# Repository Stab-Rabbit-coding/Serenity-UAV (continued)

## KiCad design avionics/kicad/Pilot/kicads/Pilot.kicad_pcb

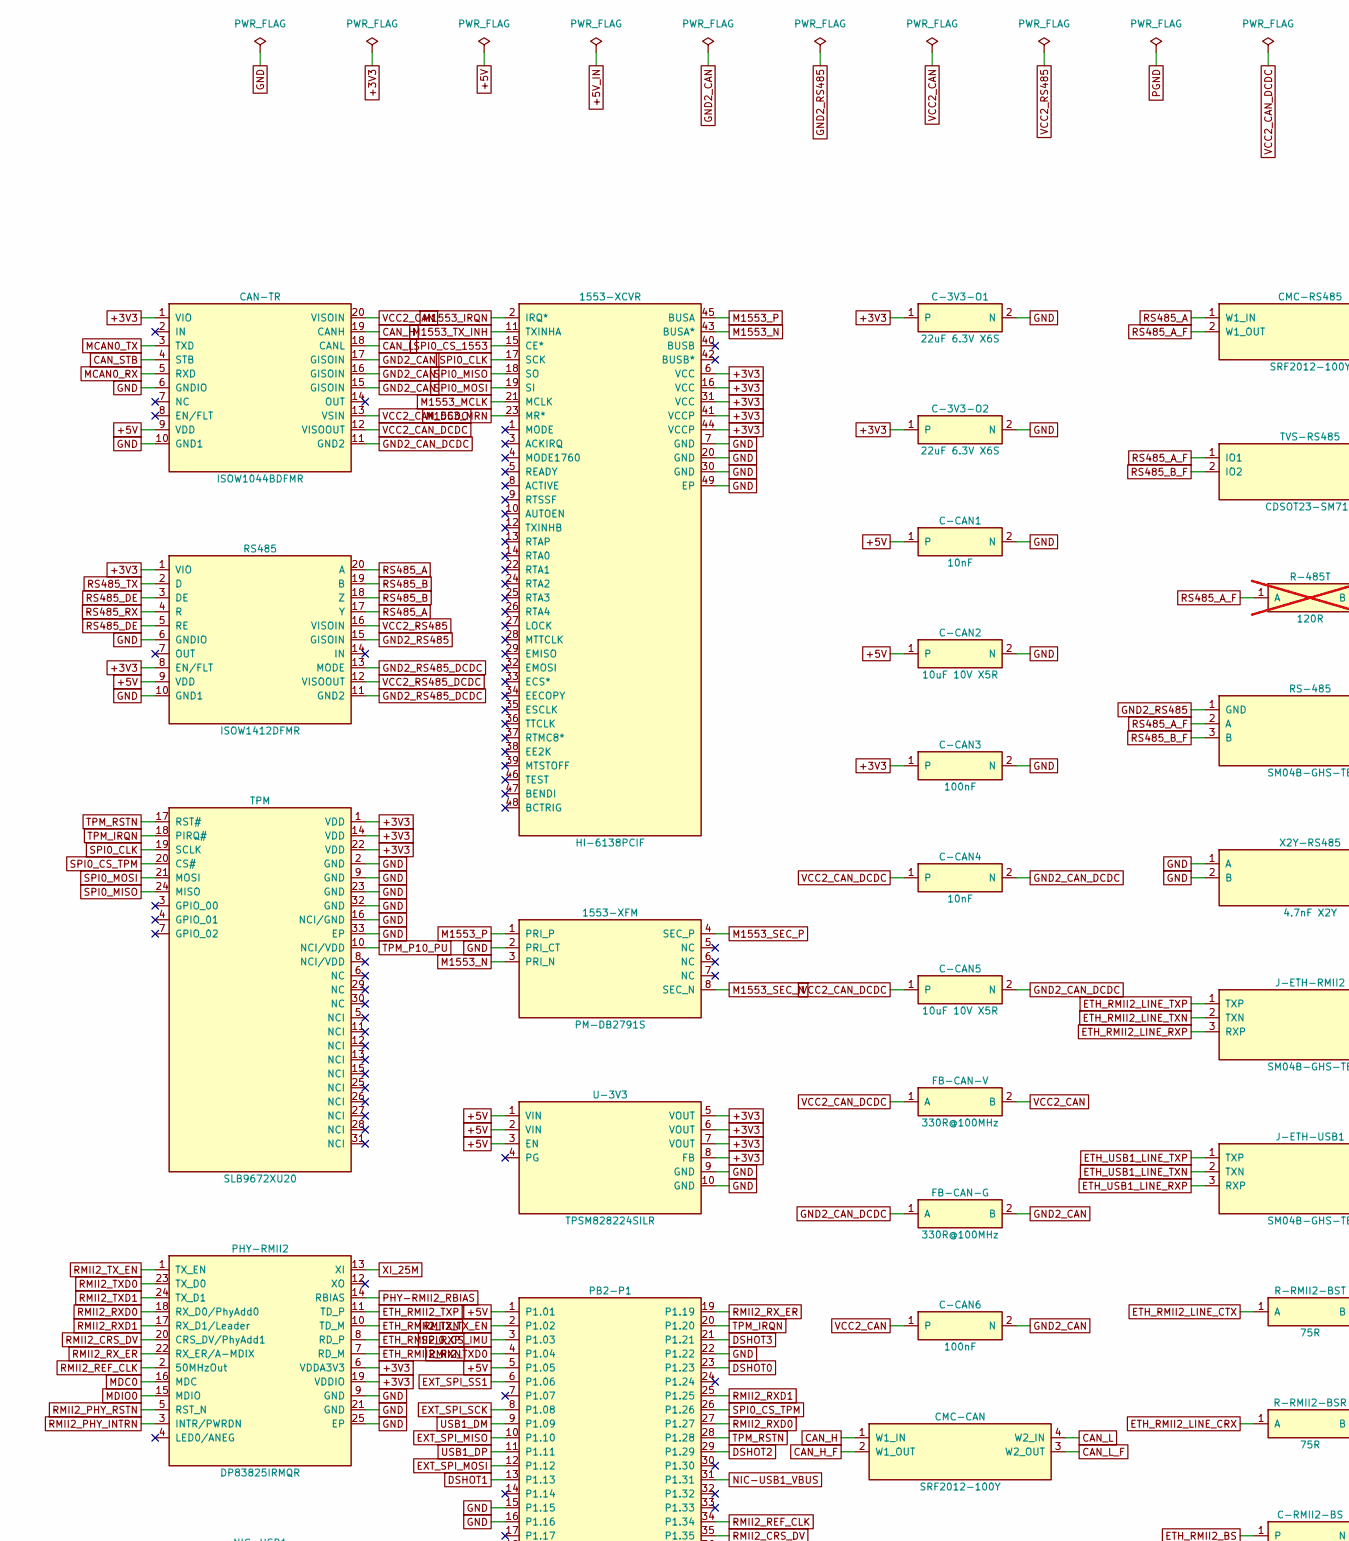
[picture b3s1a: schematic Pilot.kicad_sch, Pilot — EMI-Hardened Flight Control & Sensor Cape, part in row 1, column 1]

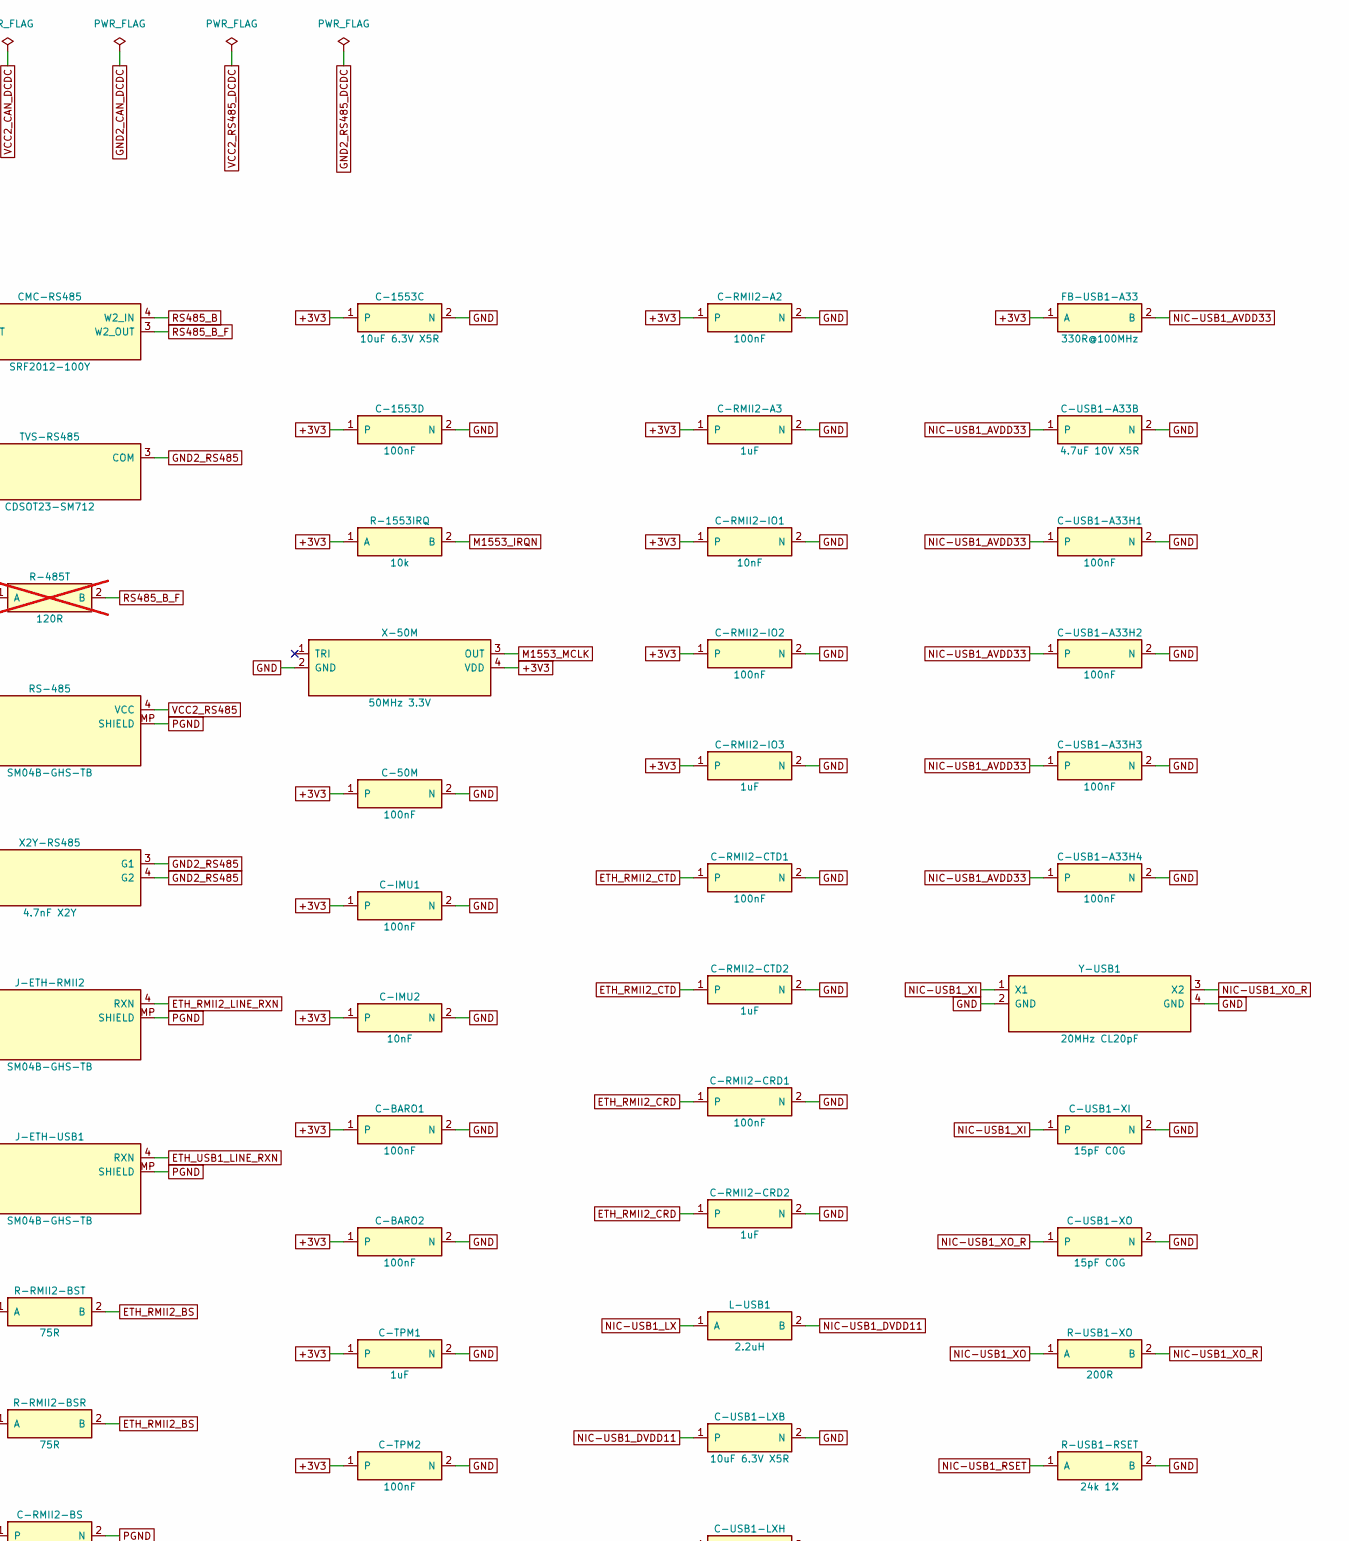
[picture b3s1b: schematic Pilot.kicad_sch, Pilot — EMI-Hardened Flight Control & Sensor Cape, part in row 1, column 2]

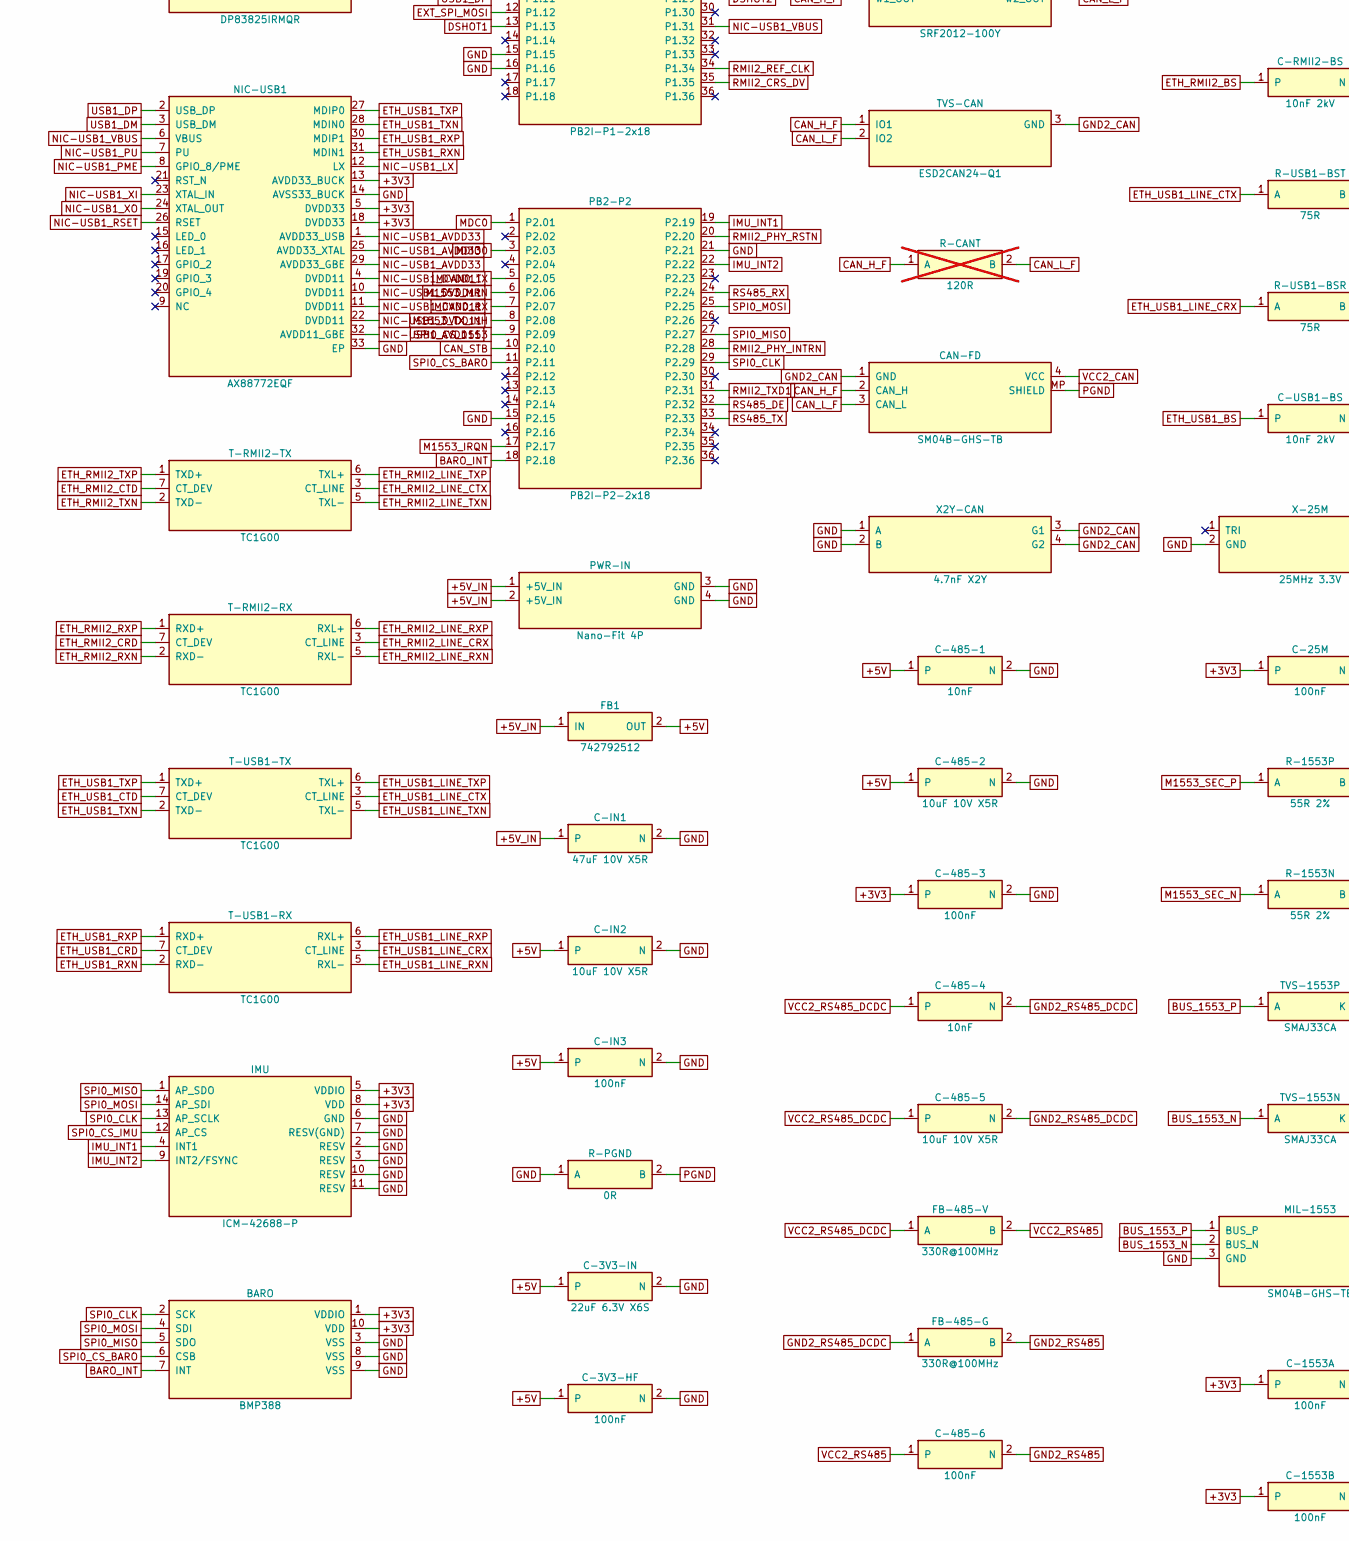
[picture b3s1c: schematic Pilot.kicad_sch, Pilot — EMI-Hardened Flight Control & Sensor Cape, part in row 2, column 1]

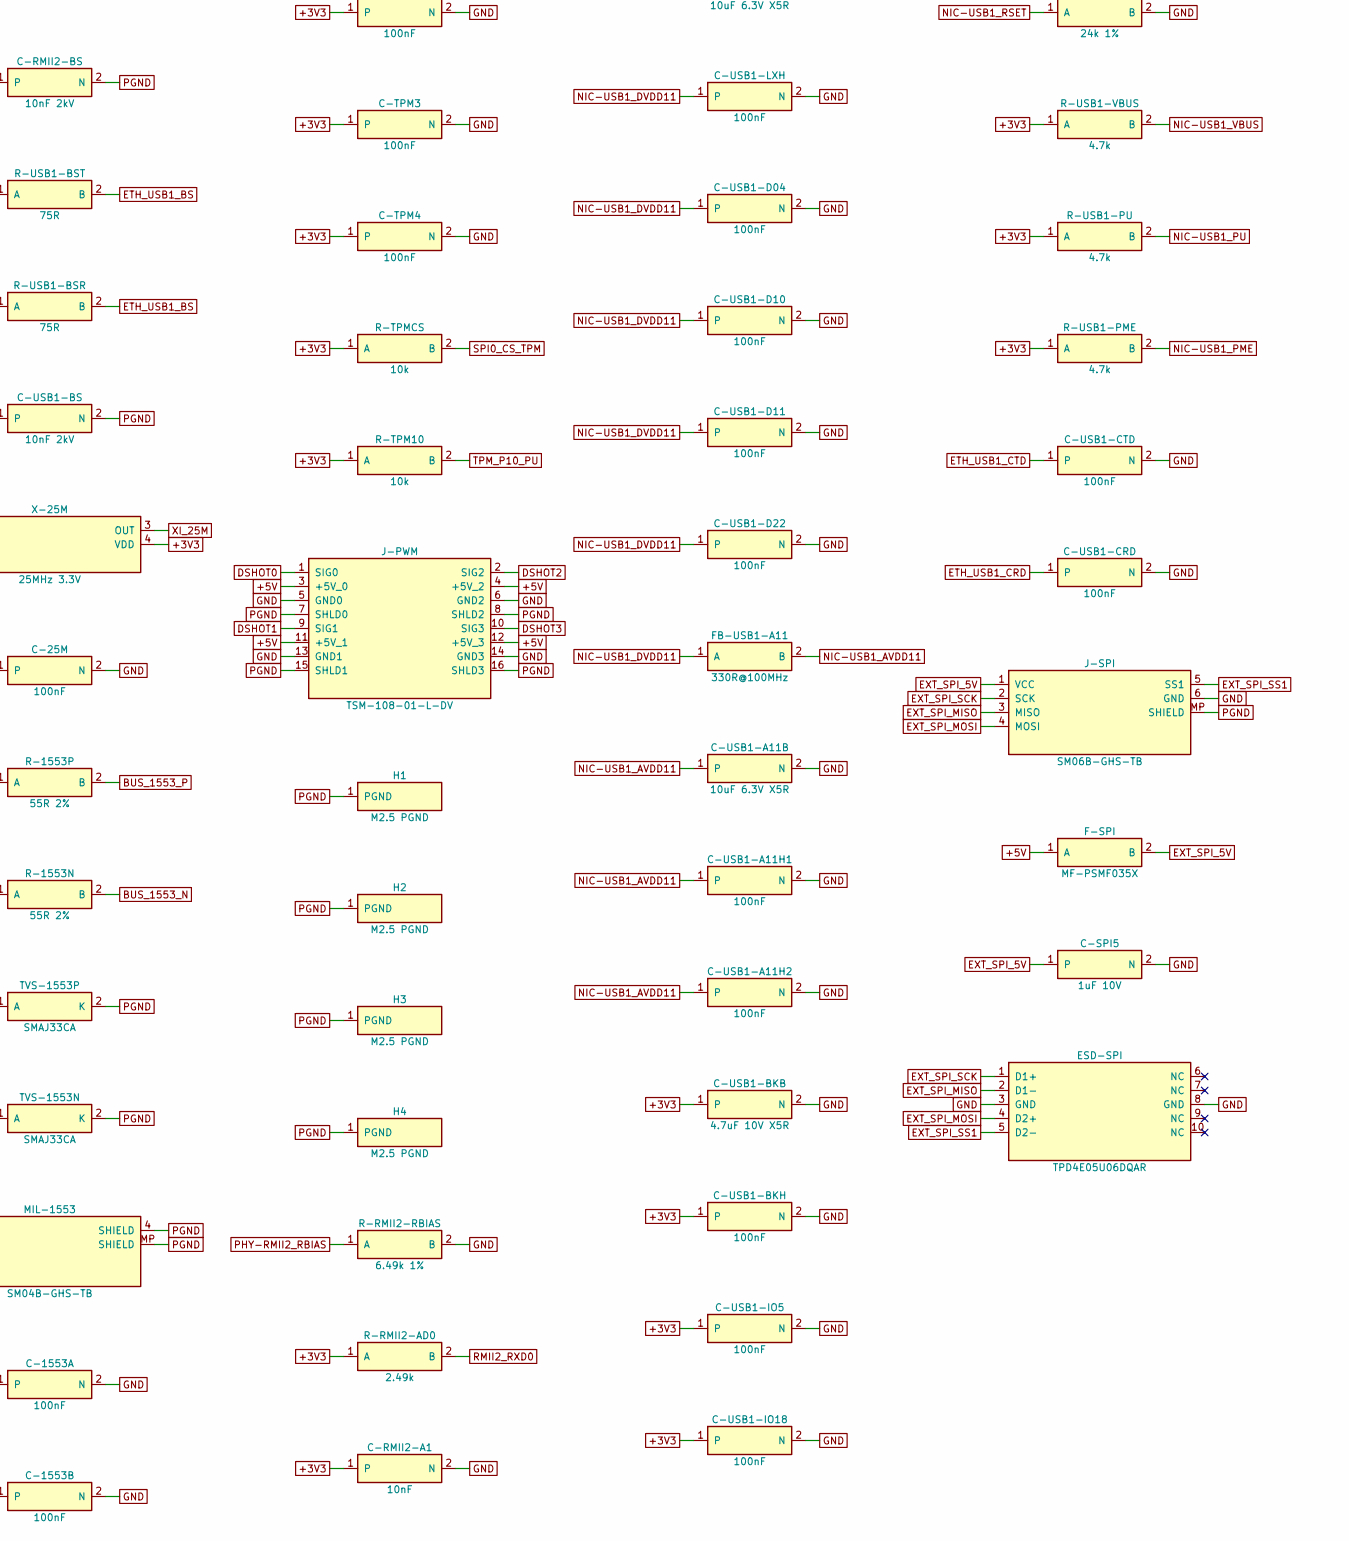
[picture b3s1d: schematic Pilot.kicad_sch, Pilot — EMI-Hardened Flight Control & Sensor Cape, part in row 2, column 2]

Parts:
1553-XCVR: HI-6138PCIF; Holt_HI-6138_QFN-48_6x6mm_P0.4mm_EP4.6mm; MPN HI-6138PCIF
1553-XFM: PM-DB2791S; Xfmr_1553_SMD_0.40in_8pin; MPN PM-DB2791S
BARO: BMP388; Bosch_BMP388_LGA-10_2x2mm; MPN BMP388
C-3V3-HF, C-25M, C-50M, C-485-3, C-485-6, C-1553A, C-1553B, C-1553D: 100nF; C_0402_1005Metric; MPN CC0402KRX7R7BB104
C-3V3-IN, C-3V3-O1, C-3V3-O2: 22uF 6.3V X6S; C_0603_1608Metric; MPN MSASJ168BC6226MTNA01
C-485-1, C-485-4: 10nF; C_0402_1005Metric; MPN CC0402KRX7R7BB103
C-485-2, C-485-5: 10uF 10V X5R; C_0805_2012Metric; MPN CC0805KKX5R6BB106
C-1553C: 10uF 6.3V X5R; C_0805_2012Metric; MPN CC0805KKX5R6BB106
C-BARO1, C-BARO2: 100nF; C_0402_1005Metric; MPN CC0402KRX7R7BB104
C-CAN1, C-CAN4: 10nF; C_0402_1005Metric; MPN CC0402KRX7R7BB103
C-CAN2, C-CAN5: 10uF 10V X5R; C_0805_2012Metric; MPN CC0805KKX5R6BB106
C-CAN3, C-CAN6: 100nF; C_0402_1005Metric; MPN CC0402KRX7R7BB104
C-IMU1: 100nF; C_0402_1005Metric; MPN CC0402KRX7R7BB104
C-IMU2: 10nF; C_0201_0603Metric; MPN CC0201KRX7R7BB103
C-IN1: 47uF 10V X5R; C_1210_3225Metric; MPN LMK325BJ476KMHP
C-IN2: 10uF 10V X5R; C_0805_2012Metric; MPN CC0805KKX5R6BB106
C-IN3: 100nF; C_0402_1005Metric; MPN CC0402KRX7R7BB104
C-RMII2-A1, C-RMII2-IO1: 10nF; C_0201_0603Metric; MPN CC0201KRX7R7BB103
C-RMII2-A2, C-RMII2-CRD1, C-RMII2-CTD1, C-RMII2-IO2: 100nF; C_0402_1005Metric; MPN CC0402KRX7R7BB104
C-RMII2-A3, C-RMII2-CRD2, C-RMII2-CTD2, C-RMII2-IO3: 1uF; C_0402_1005Metric; MPN CC0402KRX5R6BB105
C-RMII2-BS: 10nF 2kV; C_1808_4520Metric; MPN C1808X103K202T
C-SPI5: 1uF 10V; C_0402_1005Metric; MPN CC0402KRX5R6BB105
C-TPM1: 1uF; C_0402_1005Metric; MPN CC0402KRX5R6BB105
C-TPM2, C-TPM3, C-TPM4: 100nF; C_0402_1005Metric; MPN CC0402KRX7R7BB104
C-USB1-A11B, C-USB1-LXB: 10uF 6.3V X5R; C_0603_1608Metric; MPN CC0603KRX5R5BB106
C-USB1-A11H1, C-USB1-A11H2, C-USB1-A33H1, C-USB1-A33H2, C-USB1-A33H3, C-USB1-A33H4, C-USB1-BKH, C-USB1-D04, C-USB1-D10, C-USB1-D11, C-USB1-D22, C-USB1-IO5, C-USB1-IO18, C-USB1-LXH: 100nF; C_0201_0603Metric; MPN CC0201KRX5R6BB104
C-USB1-A33B, C-USB1-BKB: 4.7uF 10V X5R; C_0603_1608Metric; MPN CC0603MRX5R6BB475
C-USB1-BS: 10nF 2kV; C_1808_4520Metric; MPN C1808X103K202T
C-USB1-CRD, C-USB1-CTD: 100nF; C_0402_1005Metric; MPN CC0402KRX7R7BB104
C-USB1-XI, C-USB1-XO: 15pF C0G; C_0402_1005Metric; MPN CC0402JRNPO9BN150
CAN-FD: SM04B-GHS-TB; JST_GH_SM04B-GHS-TB_1x04-1MP_P1.25mm_Horizontal; MPN SM04B-GHS-TB(LF)(SN)
CAN-TR: ISOW1044BDFMR; SOIC-20W_7.5x12.8mm_P1.27mm; MPN ISOW1044BDFMR
CMC-CAN: SRF2012-100Y; Bourns_SRF2012_4T; MPN SRF2012-121YA
CMC-RS485: SRF2012-100Y; Bourns_SRF2012_4T; MPN SRF2012-121YA
ESD-SPI: TPD4E05U06DQAR; TI_DQA0010A_USON-10_2.5x1.0mm_P0.5mm; MPN TPD4E05U06DQAR
F-SPI: MF-PSMF035X; Fuse_0805_2012Metric; MPN MF-PSMF035X-2
FB1: 742792512; L_0805_2012Metric; MPN 742792512
FB-485-G, FB-485-V: 330R@100MHz; L_0402_1005Metric; MPN BLM15EX331SN1D
FB-CAN-G: 330R@100MHz; L_0402_1005Metric; MPN BLM15EX331SN1D
FB-CAN-V: 330R@100MHz; L_0402_1005Metric; MPN BLM15EX331SN1D
FB-USB1-A11, FB-USB1-A33: 330R@100MHz; L_0402_1005Metric; MPN BLM15EX331SN1D
H1, H2, H3, H4: M2.5 PGND; MountingHole_2.7mm_M2.5_PGND_Ring
IMU: ICM-42688-P; Bosch_LGA-14_3x2.5mm_P0.5mm; MPN ICM-42688-P
J-ETH-RMII2: SM04B-GHS-TB; JST_GH_SM04B-GHS-TB_1x04-1MP_P1.25mm_Horizontal; MPN SM04B-GHS-TB(LF)(SN)
J-ETH-USB1: SM04B-GHS-TB; JST_GH_SM04B-GHS-TB_1x04-1MP_P1.25mm_Horizontal; MPN SM04B-GHS-TB(LF)(SN)
J-PWM: TSM-108-01-L-DV; Samtec_TSM-108-01-x-DV; MPN TSM-108-01-L-DV
J-SPI: SM06B-GHS-TB; JST_GH_SM06B-GHS-TB_1x06-1MP_P1.25mm_Horizontal; MPN SM06B-GHS-TB(LF)(SN)
L-USB1: 2.2uH; L_Murata_DFE201610P; MPN DFE201610P-2R2M=P2
MIL-1553: SM04B-GHS-TB; JST_GH_SM04B-GHS-TB_1x04-1MP_P1.25mm_Horizontal; MPN SM04B-GHS-TB(LF)(SN)
NIC-USB1: AX88772EQF; QFN-32-1EP_4x4mm_P0.4mm_EP2.9x2.9mm; MPN AX88772EQF
PB2-P1: PB2I-P1-2x18; PocketBeagle2_2x18_P1_TSM-DV-LC; MPN TSM-118-04-L-DV-LC
PB2-P2: PB2I-P2-2x18; PocketBeagle2_2x18_P2_TSM-DV-LC; MPN TSM-118-04-L-DV-LC
PHY-RMII2: DP83825IRMQR; Texas_RMQ0024A_WQFN-24-1EP_3x3mm_P0.4mm_EP1.9x1.9mm; MPN DP83825IRMQR
PWR-IN: Nano-Fit 4P; Molex_NanoFit_1x04_Horizontal; MPN 105313-1204
R-485T: 120R; R_0603_1608Metric; MPN RC0603FR-07120RL; not fitted
R-1553IRQ: 10k; R_0402_1005Metric; MPN RC0402FR-0710KL
R-1553N, R-1553P: 55R 2%; R_0603_1608Metric; MPN RC0603FR-0754R9L
R-CANT: 120R; R_0603_1608Metric; MPN RC0603FR-07120RL; not fitted
R-PGND: 0R; R_0805_2012Metric; MPN RC0805JR-070RL
R-RMII2-AD0: 2.49k; R_0201_0603Metric; MPN RC0201FR-072K49P
R-RMII2-BSR, R-RMII2-BST: 75R; R_0402_1005Metric; MPN RC0402FR-0775RL
R-RMII2-RBIAS: 6.49k 1%; R_0201_0603Metric; MPN RC0201FR-076K49L
R-TPM10: 10k; R_0201_0603Metric; MPN RC0201FR-0710KL
R-TPMCS: 10k; R_0201_0603Metric; MPN RC0201FR-0710KL
R-USB1-BSR, R-USB1-BST: 75R; R_0402_1005Metric; MPN RC0402FR-0775RL
R-USB1-PME, R-USB1-PU, R-USB1-VBUS: 4.7k; R_0201_0603Metric; MPN RC0201FR-074K7L
R-USB1-RSET: 24k 1%; R_0402_1005Metric; MPN RC0402FR-0724KL
R-USB1-XO: 200R; R_0402_1005Metric; MPN RC0402FR-07200RP
RS485: ISOW1412DFMR; SOIC-20W_7.5x12.8mm_P1.27mm; MPN ISOW1412DFMR
RS-485: SM04B-GHS-TB; JST_GH_SM04B-GHS-TB_1x04-1MP_P1.25mm_Horizontal; MPN SM04B-GHS-TB(LF)(SN)
T-RMII2-RX, T-RMII2-TX: TC1G00; Pulse_TC1G00_PulseChip_4.7x3.2mm; MPN TC1G00
T-USB1-RX, T-USB1-TX: TC1G00; Pulse_TC1G00_PulseChip_4.7x3.2mm; MPN TC1G00
TPM: SLB9672XU20; QFN-32-1EP_5x5mm_P0.5mm_EP3.6x3.6mm; MPN SLB9672XU20FW1611XUMA1
TVS-1553N, TVS-1553P: SMAJ33CA; D_SMA; MPN SMAJ33CA
TVS-CAN: ESD2CAN24-Q1; SOT-323_SC-70; MPN ESD2CAN24DCKRQ1
TVS-RS485: CDSOT23-SM712; SOT-23; MPN CDSOT23-SM712
U-3V3: TPSM828224SILR; TI_SIL0010D_uSiP-10_2.0x2.5mm_P0.5mm; MPN TPSM828224SILR
X2Y-CAN, X2Y-RS485: 4.7nF X2Y; X2Y_0805_4T; MPN CX0805MRX7R0BB472
X-25M: 25MHz 3.3V; Oscillator_SMD_ECS_2520MV-xxx-xx-4Pin_2.5x2.0mm; MPN ECS-2520MV-250-BN-TR
X-50M: 50MHz 3.3V; Oscillator_SMD_ECS_2520MV-xxx-xx-4Pin_2.5x2.0mm; MPN ECS-2520MV-500-BN-TR
Y-USB1: 20MHz CL20pF; Crystal_SMD_3225-4Pin_3.2x2.5mm; MPN ECS-200-20-33-AGM-TR

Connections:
+3V3: 1553-XCVR.6 (VCC), 1553-XCVR.16 (VCC), 1553-XCVR.31 (VCC), 1553-XCVR.41 (VCCP), 1553-XCVR.44 (VCCP), BARO.1 (VDDIO), BARO.10 (VDD), C-3V3-O1.1, C-3V3-O2.1, C-25M.1, C-50M.1, C-485-3.1, C-1553A.1, C-1553B.1, C-1553C.1, C-1553D.1, C-BARO1.1, C-BARO2.1, C-CAN3.1, C-IMU1.1, C-IMU2.1, C-RMII2-A1.1, C-RMII2-A2.1, C-RMII2-A3.1, C-RMII2-IO1.1, C-RMII2-IO2.1, C-RMII2-IO3.1, C-TPM1.1, C-TPM2.1, C-TPM3.1, C-TPM4.1, C-USB1-BKB.1, C-USB1-BKH.1, C-USB1-IO5.1, C-USB1-IO18.1, CAN-TR.1 (VIO), FB-USB1-A33.1 (A), IMU.5 (VDDIO), IMU.8 (VDD), NIC-USB1.5 (DVDD33), NIC-USB1.13 (AVDD33_BUCK), NIC-USB1.18 (DVDD33), PHY-RMII2.6 (VDDA3V3), PHY-RMII2.19 (VDDIO), R-1553IRQ.1 (A), R-RMII2-AD0.1 (A), R-TPM10.1 (A), R-TPMCS.1 (A), R-USB1-PME.1 (A), R-USB1-PU.1 (A), R-USB1-VBUS.1 (A), RS485.1 (VIO), RS485.8 (EN/FLT), TPM.1 (VDD), TPM.14 (VDD), TPM.22 (VDD), U-3V3.5 (VOUT), U-3V3.6 (VOUT), U-3V3.7 (VOUT), U-3V3.8 (FB), X-25M.4 (VDD), X-50M.4 (VDD)
+5V: C-3V3-HF.1, C-3V3-IN.1, C-485-1.1, C-485-2.1, C-CAN1.1, C-CAN2.1, C-IN2.1, C-IN3.1, CAN-TR.9 (VDD), F-SPI.1 (A), FB1.2 (OUT), J-PWM.3 (+5V_0), J-PWM.4 (+5V_2), J-PWM.11 (+5V_1), J-PWM.12 (+5V_3), PB2-P1.1 (P1.01), PB2-P1.5 (P1.05), RS485.9 (VDD), U-3V3.1 (VIN), U-3V3.2 (VIN), U-3V3.3 (EN)
+5V_IN: C-IN1.1, FB1.1 (IN), PWR-IN.1 (+5V_IN), PWR-IN.2 (+5V_IN)
BARO_INT: BARO.7 (INT), PB2-P2.18 (P2.18)
BUS_1553_N: MIL-1553.2 (BUS_N), R-1553N.2 (B), TVS-1553N.1 (A)
BUS_1553_P: MIL-1553.1 (BUS_P), R-1553P.2 (B), TVS-1553P.1 (A)
CAN_H: CAN-TR.19 (CANH), CMC-CAN.1 (W1_IN)
CAN_H_F: CAN-FD.2 (CAN_H), CMC-CAN.2 (W1_OUT), R-CANT.1 (A), TVS-CAN.1 (IO1)
CAN_L: CAN-TR.18 (CANL), CMC-CAN.4 (W2_IN)
CAN_L_F: CAN-FD.3 (CAN_L), CMC-CAN.3 (W2_OUT), R-CANT.2 (B), TVS-CAN.2 (IO2)
CAN_STB: CAN-TR.4 (STB), PB2-P2.10 (P2.10)
DSHOT0: J-PWM.1 (SIG0), PB2-P1.23 (P1.23)
DSHOT1: J-PWM.9 (SIG1), PB2-P1.13 (P1.13)
DSHOT2: J-PWM.2 (SIG2), PB2-P1.29 (P1.29)
DSHOT3: J-PWM.10 (SIG3), PB2-P1.21 (P1.21)
ETH_RMII2_BS: C-RMII2-BS.1, R-RMII2-BSR.2 (B), R-RMII2-BST.2 (B)
ETH_RMII2_CRD: C-RMII2-CRD1.1, C-RMII2-CRD2.1, T-RMII2-RX.7 (CT_DEV)
ETH_RMII2_CTD: C-RMII2-CTD1.1, C-RMII2-CTD2.1, T-RMII2-TX.7 (CT_DEV)
ETH_RMII2_LINE_CRX: R-RMII2-BSR.1 (A), T-RMII2-RX.3 (CT_LINE)
ETH_RMII2_LINE_CTX: R-RMII2-BST.1 (A), T-RMII2-TX.3 (CT_LINE)
ETH_RMII2_LINE_RXN: J-ETH-RMII2.4 (RXN), T-RMII2-RX.5 (RXL-)
ETH_RMII2_LINE_RXP: J-ETH-RMII2.3 (RXP), T-RMII2-RX.6 (RXL+)
ETH_RMII2_LINE_TXN: J-ETH-RMII2.2 (TXN), T-RMII2-TX.5 (TXL-)
ETH_RMII2_LINE_TXP: J-ETH-RMII2.1 (TXP), T-RMII2-TX.6 (TXL+)
ETH_RMII2_RXN: PHY-RMII2.7 (RD_M), T-RMII2-RX.2 (RXD-)
ETH_RMII2_RXP: PHY-RMII2.8 (RD_P), T-RMII2-RX.1 (RXD+)
ETH_RMII2_TXN: PHY-RMII2.10 (TD_M), T-RMII2-TX.2 (TXD-)
ETH_RMII2_TXP: PHY-RMII2.11 (TD_P), T-RMII2-TX.1 (TXD+)
ETH_USB1_BS: C-USB1-BS.1, R-USB1-BSR.2 (B), R-USB1-BST.2 (B)
ETH_USB1_CRD: C-USB1-CRD.1, T-USB1-RX.7 (CT_DEV)
ETH_USB1_CTD: C-USB1-CTD.1, T-USB1-TX.7 (CT_DEV)
ETH_USB1_LINE_CRX: R-USB1-BSR.1 (A), T-USB1-RX.3 (CT_LINE)
ETH_USB1_LINE_CTX: R-USB1-BST.1 (A), T-USB1-TX.3 (CT_LINE)
ETH_USB1_LINE_RXN: J-ETH-USB1.4 (RXN), T-USB1-RX.5 (RXL-)
ETH_USB1_LINE_RXP: J-ETH-USB1.3 (RXP), T-USB1-RX.6 (RXL+)
ETH_USB1_LINE_TXN: J-ETH-USB1.2 (TXN), T-USB1-TX.5 (TXL-)
ETH_USB1_LINE_TXP: J-ETH-USB1.1 (TXP), T-USB1-TX.6 (TXL+)
ETH_USB1_RXN: NIC-USB1.31 (MDIN1), T-USB1-RX.2 (RXD-)
ETH_USB1_RXP: NIC-USB1.30 (MDIP1), T-USB1-RX.1 (RXD+)
ETH_USB1_TXN: NIC-USB1.28 (MDIN0), T-USB1-TX.2 (TXD-)
ETH_USB1_TXP: NIC-USB1.27 (MDIP0), T-USB1-TX.1 (TXD+)
EXT_SPI_5V: C-SPI5.1, F-SPI.2 (B), J-SPI.1 (VCC)
EXT_SPI_MISO: ESD-SPI.2 (D1-), J-SPI.3 (MISO), PB2-P1.10 (P1.10)
EXT_SPI_MOSI: ESD-SPI.4 (D2+), J-SPI.4 (MOSI), PB2-P1.12 (P1.12)
EXT_SPI_SCK: ESD-SPI.1 (D1+), J-SPI.2 (SCK), PB2-P1.8 (P1.08)
EXT_SPI_SS1: ESD-SPI.5 (D2-), J-SPI.5 (SS1), PB2-P1.6 (P1.06)
GND: 1553-XCVR.7 (GND), 1553-XCVR.20 (GND), 1553-XCVR.30 (GND), 1553-XCVR.49 (EP), 1553-XFM.2 (PRI_CT), BARO.3 (VSS), BARO.8 (VSS), BARO.9 (VSS), C-3V3-HF.2 (N), C-3V3-IN.2 (N), C-3V3-O1.2 (N), C-3V3-O2.2 (N), C-25M.2 (N), C-50M.2 (N), C-485-1.2 (N), C-485-2.2 (N), C-485-3.2 (N), C-1553A.2 (N), C-1553B.2 (N), C-1553C.2 (N), C-1553D.2 (N), C-BARO1.2 (N), C-BARO2.2 (N), C-CAN1.2 (N), C-CAN2.2 (N), C-CAN3.2 (N), C-IMU1.2 (N), C-IMU2.2 (N), C-IN1.2 (N), C-IN2.2 (N), C-IN3.2 (N), C-RMII2-A1.2 (N), C-RMII2-A2.2 (N), C-RMII2-A3.2 (N), C-RMII2-CRD1.2 (N), C-RMII2-CRD2.2 (N), C-RMII2-CTD1.2 (N), C-RMII2-CTD2.2 (N), C-RMII2-IO1.2 (N), C-RMII2-IO2.2 (N), C-RMII2-IO3.2 (N), C-SPI5.2 (N), C-TPM1.2 (N), C-TPM2.2 (N), C-TPM3.2 (N), C-TPM4.2 (N), C-USB1-A11B.2 (N), C-USB1-A11H1.2 (N), C-USB1-A11H2.2 (N), C-USB1-A33B.2 (N), C-USB1-A33H1.2 (N), C-USB1-A33H2.2 (N), C-USB1-A33H3.2 (N), C-USB1-A33H4.2 (N), C-USB1-BKB.2 (N), C-USB1-BKH.2 (N), C-USB1-CRD.2 (N), C-USB1-CTD.2 (N), C-USB1-D04.2 (N), C-USB1-D10.2 (N), C-USB1-D11.2 (N), C-USB1-D22.2 (N), C-USB1-IO5.2 (N), C-USB1-IO18.2 (N), C-USB1-LXB.2 (N), C-USB1-LXH.2 (N), C-USB1-XI.2 (N), C-USB1-XO.2 (N), CAN-TR.6 (GNDIO), CAN-TR.10 (GND1), ESD-SPI.3 (GND), ESD-SPI.8 (GND), IMU.2 (RESV), IMU.3 (RESV), IMU.6 (GND), IMU.7 (RESV(GND)), IMU.10 (RESV), IMU.11 (RESV), J-PWM.5 (GND0), J-PWM.6 (GND2), J-PWM.13 (GND1), J-PWM.14 (GND3), J-SPI.6 (GND), MIL-1553.3 (GND), NIC-USB1.14 (AVSS33_BUCK), NIC-USB1.33 (EP), PB2-P1.15 (P1.15), PB2-P1.16 (P1.16), PB2-P1.22 (P1.22), PB2-P2.15 (P2.15), PB2-P2.21 (P2.21), PHY-RMII2.9 (GND), PHY-RMII2.21 (GND), PHY-RMII2.25 (EP), PWR-IN.3 (GND), PWR-IN.4 (GND), R-PGND.1 (A), R-RMII2-RBIAS.2 (B), R-USB1-RSET.2 (B), RS485.6 (GNDIO), RS485.10 (GND1), TPM.2 (GND), TPM.9 (GND), TPM.16 (NCI/GND), TPM.23 (GND), TPM.32 (GND), TPM.33 (EP), U-3V3.9 (GND), U-3V3.10 (GND), X2Y-CAN.1 (A), X2Y-CAN.2 (B), X2Y-RS485.1 (A), X2Y-RS485.2 (B), X-25M.2 (GND), X-50M.2 (GND), Y-USB1.2 (GND), Y-USB1.4 (GND)
GND2_CAN: C-CAN6.2 (N), CAN-FD.1 (GND), CAN-TR.15 (GISOIN), CAN-TR.16 (GISOIN), CAN-TR.17 (GISOIN), FB-CAN-G.2 (B), TVS-CAN.3 (GND), X2Y-CAN.3 (G1), X2Y-CAN.4 (G2)
GND2_CAN_DCDC: C-CAN4.2 (N), C-CAN5.2 (N), CAN-TR.11 (GND2), FB-CAN-G.1 (A)
GND2_RS485: C-485-6.2 (N), FB-485-G.2 (B), RS485.15 (GISOIN), RS-485.1 (GND), TVS-RS485.3 (COM), X2Y-RS485.3 (G1), X2Y-RS485.4 (G2)
GND2_RS485_DCDC: C-485-4.2 (N), C-485-5.2 (N), FB-485-G.1 (A), RS485.11 (GND2), RS485.13 (MODE)
IMU_INT1: IMU.4 (INT1), PB2-P2.19 (P2.19)
IMU_INT2: IMU.9 (INT2/FSYNC), PB2-P2.22 (P2.22)
M1553_IRQN: 1553-XCVR.2 (IRQ*), PB2-P2.17 (P2.17), R-1553IRQ.2 (B)
M1553_MCLK: 1553-XCVR.21 (MCLK), X-50M.3 (OUT)
M1553_MRN: 1553-XCVR.23 (MR*), PB2-P2.6 (P2.06)
M1553_N: 1553-XCVR.43 (BUSA*), 1553-XFM.3 (PRI_N)
M1553_P: 1553-XCVR.45 (BUSA), 1553-XFM.1 (PRI_P)
M1553_SEC_N: 1553-XFM.8 (SEC_N), R-1553N.1 (A)
M1553_SEC_P: 1553-XFM.4 (SEC_P), R-1553P.1 (A)
M1553_TX_INH: 1553-XCVR.11 (TXINHA), PB2-P2.8 (P2.08)
MCAN0_RX: CAN-TR.5 (RXD), PB2-P2.7 (P2.07)
MCAN0_TX: CAN-TR.3 (TXD), PB2-P2.5 (P2.05)
MDC0: PB2-P2.1 (P2.01), PHY-RMII2.16 (MDC)
MDIO0: PB2-P2.3 (P2.03), PHY-RMII2.15 (MDIO)
NIC-USB1_AVDD11: C-USB1-A11B.1, C-USB1-A11H1.1, C-USB1-A11H2.1, FB-USB1-A11.2 (B), NIC-USB1.32 (AVDD11_GBE)
NIC-USB1_AVDD33: C-USB1-A33B.1, C-USB1-A33H1.1, C-USB1-A33H2.1, C-USB1-A33H3.1, C-USB1-A33H4.1, FB-USB1-A33.2 (B), NIC-USB1.1 (AVDD33_USB), NIC-USB1.25 (AVDD33_XTAL), NIC-USB1.29 (AVDD33_GBE)
NIC-USB1_DVDD11: C-USB1-D04.1, C-USB1-D10.1, C-USB1-D11.1, C-USB1-D22.1, C-USB1-LXB.1, C-USB1-LXH.1, FB-USB1-A11.1 (A), L-USB1.2 (B), NIC-USB1.4 (DVDD11), NIC-USB1.10 (DVDD11), NIC-USB1.11 (DVDD11), NIC-USB1.22 (DVDD11)
NIC-USB1_LX: L-USB1.1 (A), NIC-USB1.12 (LX)
NIC-USB1_PME: NIC-USB1.8 (GPIO_8/PME), R-USB1-PME.2 (B)
NIC-USB1_PU: NIC-USB1.7 (PU), R-USB1-PU.2 (B)
NIC-USB1_RSET: NIC-USB1.26 (RSET), R-USB1-RSET.1 (A)
NIC-USB1_VBUS: NIC-USB1.6 (VBUS), PB2-P1.31 (P1.31), R-USB1-VBUS.2 (B)
NIC-USB1_XI: C-USB1-XI.1, NIC-USB1.23 (XTAL_IN), Y-USB1.1 (X1)
NIC-USB1_XO: NIC-USB1.24 (XTAL_OUT), R-USB1-XO.1 (A)
NIC-USB1_XO_R: C-USB1-XO.1, R-USB1-XO.2 (B), Y-USB1.3 (X2)
PGND: C-RMII2-BS.2 (N), C-USB1-BS.2 (N), CAN-FD.MP (SHIELD), H1.1, H2.1, H3.1, H4.1, J-ETH-RMII2.MP (SHIELD), J-ETH-USB1.MP (SHIELD), J-PWM.7 (SHLD0), J-PWM.8 (SHLD2), J-PWM.15 (SHLD1), J-PWM.16 (SHLD3), J-SPI.MP (SHIELD), MIL-1553.4 (SHIELD), MIL-1553.MP (SHIELD), R-PGND.2 (B), RS-485.MP (SHIELD), TVS-1553N.2 (K), TVS-1553P.2 (K)
PHY-RMII2_RBIAS: PHY-RMII2.14 (RBIAS), R-RMII2-RBIAS.1 (A)
RMII2_CRS_DV: PB2-P1.35 (P1.35), PHY-RMII2.20 (CRS_DV/PhyAdd1)
RMII2_PHY_INTRN: PB2-P2.28 (P2.28), PHY-RMII2.3 (INTR/PWRDN)
RMII2_PHY_RSTN: PB2-P2.20 (P2.20), PHY-RMII2.5 (RST_N)
RMII2_REF_CLK: PB2-P1.34 (P1.34), PHY-RMII2.2 (50MHzOut)
RMII2_RXD0: PB2-P1.27 (P1.27), PHY-RMII2.18 (RX_D0/PhyAdd0), R-RMII2-AD0.2 (B)
RMII2_RXD1: PB2-P1.25 (P1.25), PHY-RMII2.17 (RX_D1/Leader)
RMII2_RX_ER: PB2-P1.19 (P1.19), PHY-RMII2.22 (RX_ER/A-MDIX)
RMII2_TXD0: PB2-P1.4 (P1.04), PHY-RMII2.23 (TX_D0)
RMII2_TXD1: PB2-P2.31 (P2.31), PHY-RMII2.24 (TX_D1)
RMII2_TX_EN: PB2-P1.2 (P1.02), PHY-RMII2.1 (TX_EN)
RS485_A: CMC-RS485.1 (W1_IN), RS485.17 (Y), RS485.20 (A)
RS485_A_F: CMC-RS485.2 (W1_OUT), R-485T.1 (A), RS-485.2 (A), TVS-RS485.1 (IO1)
RS485_B: CMC-RS485.4 (W2_IN), RS485.18 (Z), RS485.19 (B)
RS485_B_F: CMC-RS485.3 (W2_OUT), R-485T.2 (B), RS-485.3 (B), TVS-RS485.2 (IO2)
RS485_DE: PB2-P2.32 (P2.32), RS485.3 (DE), RS485.5 (RE)
RS485_RX: PB2-P2.24 (P2.24), RS485.4 (R)
RS485_TX: PB2-P2.33 (P2.33), RS485.2 (D)
SPI0_CLK: 1553-XCVR.17 (SCK), BARO.2 (SCK), IMU.13 (AP_SCLK), PB2-P2.29 (P2.29), TPM.19 (SCLK)
SPI0_CS_1553: 1553-XCVR.15 (CE*), PB2-P2.9 (P2.09)
SPI0_CS_BARO: BARO.6 (CSB), PB2-P2.11 (P2.11)
SPI0_CS_IMU: IMU.12 (AP_CS), PB2-P1.3 (P1.03)
SPI0_CS_TPM: PB2-P1.26 (P1.26), R-TPMCS.2 (B), TPM.20 (CS#)
SPI0_MISO: 1553-XCVR.18 (SO), BARO.5 (SDO), IMU.1 (AP_SDO), PB2-P2.27 (P2.27), TPM.24 (MISO)
SPI0_MOSI: 1553-XCVR.19 (SI), BARO.4 (SDI), IMU.14 (AP_SDI), PB2-P2.25 (P2.25), TPM.21 (MOSI)
TPM_IRQN: PB2-P1.20 (P1.20), TPM.18 (PIRQ#)
TPM_P10_PU: R-TPM10.2 (B), TPM.10 (NCI/VDD)
TPM_RSTN: PB2-P1.28 (P1.28), TPM.17 (RST#)
USB1_DM: NIC-USB1.3 (USB_DM), PB2-P1.9 (P1.09)
USB1_DP: NIC-USB1.2 (USB_DP), PB2-P1.11 (P1.11)
VCC2_CAN: C-CAN6.1, CAN-FD.4 (VCC), CAN-TR.20 (VISOIN), FB-CAN-V.2 (B)
VCC2_CAN_DCDC: C-CAN4.1, C-CAN5.1, CAN-TR.12 (VISOOUT), CAN-TR.13 (VSIN), FB-CAN-V.1 (A)
VCC2_RS485: C-485-6.1, FB-485-V.2 (B), RS485.16 (VISOIN), RS-485.4 (VCC)
VCC2_RS485_DCDC: C-485-4.1, C-485-5.1, FB-485-V.1 (A), RS485.12 (VISOOUT)
XI_25M: PHY-RMII2.13 (XI), X-25M.3 (OUT)

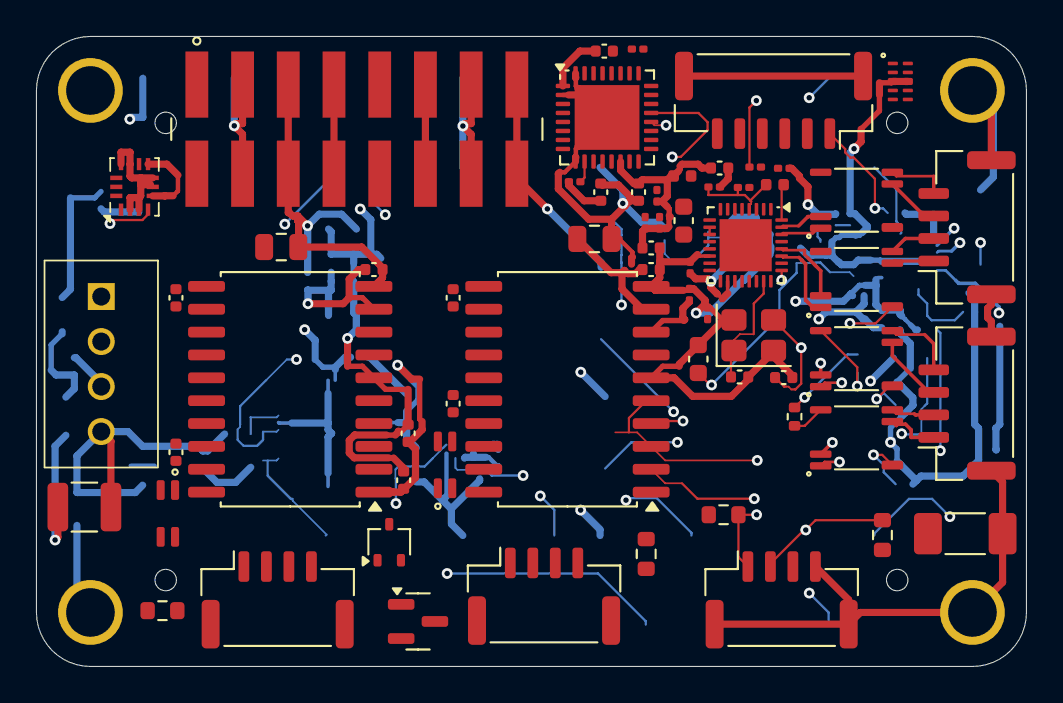
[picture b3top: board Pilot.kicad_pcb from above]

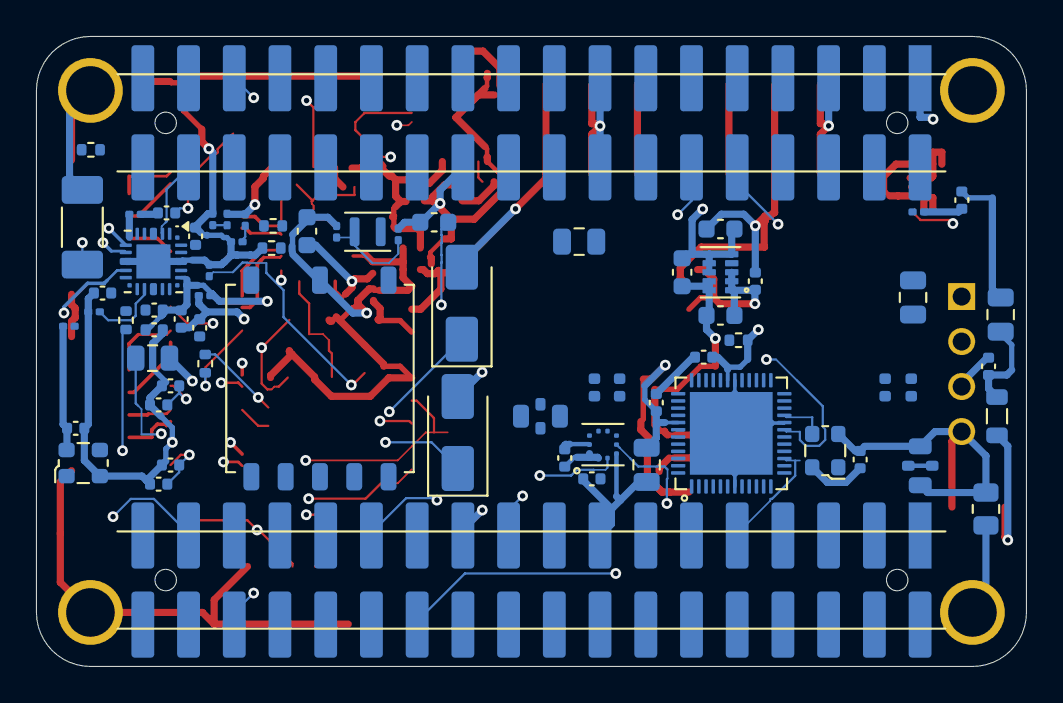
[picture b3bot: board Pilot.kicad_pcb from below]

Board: 6 copper layers, 55.0 x 35.0 mm, 136 parts (69 on the bottom side), 112 nets.
